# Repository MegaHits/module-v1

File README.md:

# MegaHits Module V1
MegaHits playback module version 1 is based on the **MS51FB9AE** 1T 8051 microcontroller.

## Why 8051?
We tested multiple platforms including AVR, MS51, RP2040, STM32F0, and MSP430. So far STM32 and MS51 sounded the best. However, due to the high lead times(5 years for some STM32 parts!), we selected MS51FB9AE 1T 8051 MCU from Nuvoton technologies. It's widely available, relatively fast, easy to develop, has tons of peripherals, and surprisingly cheap in this silicon shortage. Not only it is a sub 0.5 USD part, but also the manufacturer is giving out a discount when you purchase in small quantities.

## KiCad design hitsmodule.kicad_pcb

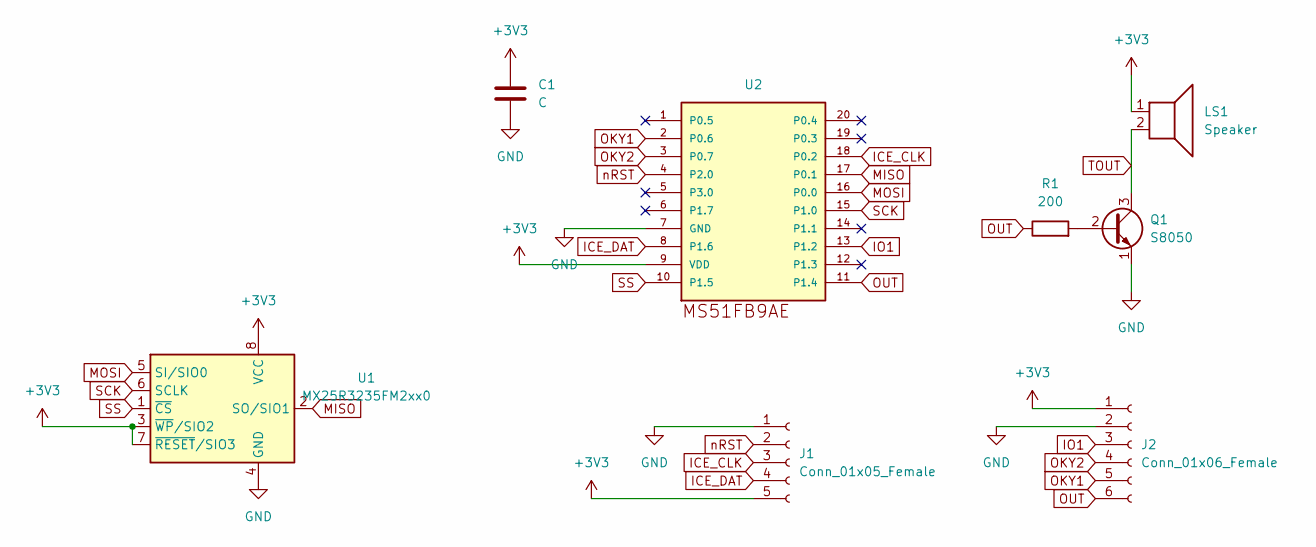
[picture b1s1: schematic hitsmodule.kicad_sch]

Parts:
C1: C; C_1206_3216Metric_Pad1.33x1.80mm_HandSolder
J1: Conn_01x05_Female; PinHeader_1x05_P2.54mm_Vertical
J2: Conn_01x06_Female; PinHeader_1x06_P2.54mm_Vertical
LS1: Speaker; R_2816_7142Metric
Q1: S8050; TO-92_Inline
R1: 200; R_Axial_DIN0204_L3.6mm_D1.6mm_P7.62mm_Horizontal
U1: MX25R3235FM2xx0; SOP-8_5.28x5.23mm_P1.27mm
U2: MS51FB9AE; TSSOP20

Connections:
+3V3: C1.1, J1.5, J2.1, LS1.1, U1.3 (~WP/SIO2), U1.7 (~RESET/SIO3), U1.8 (VCC), U2.9 (VDD)
GND: C1.2, J1.1, J2.2, Q1.1 (E), U1.4 (GND), U2.7 (GND)
ICE_CLK: J1.3, U2.18 (P0.2)
ICE_DAT: J1.4, U2.8 (P1.6)
IO1: J2.3, U2.13 (P1.2)
MISO: U1.2 (SO/SIO1), U2.17 (P0.1)
MOSI: U1.5 (SI/SIO0), U2.16 (P0.0)
unnamed: Q1.2 (B), R1.2
OKY1: J2.5, U2.2 (P0.6)
OKY2: J2.4, U2.3 (P0.7)
OUT: J2.6, R1.1, U2.11 (P1.4)
SCK: U1.6 (SCLK), U2.15 (P1.0)
SS: U1.1 (~CS), U2.10 (P1.5)
TOUT: LS1.2, Q1.3 (C)
nRST: J1.2, U2.4 (P2.0)

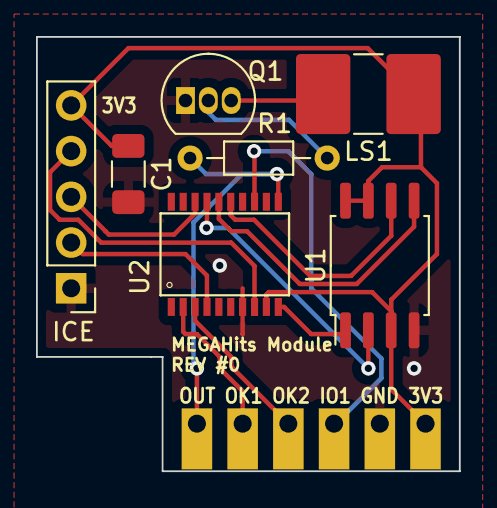
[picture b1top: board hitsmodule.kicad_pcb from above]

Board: 2 copper layers, 23.5 x 24.1 mm, 8 parts (0 on the bottom side), 15 nets.

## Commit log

2022-02-07 init commit
2022-03-18 Add firmware file
2022-03-18 Revert "Add firmware file"
    This reverts commit a0de85ef5f940c8efb14f2d825176c3f65304549.
